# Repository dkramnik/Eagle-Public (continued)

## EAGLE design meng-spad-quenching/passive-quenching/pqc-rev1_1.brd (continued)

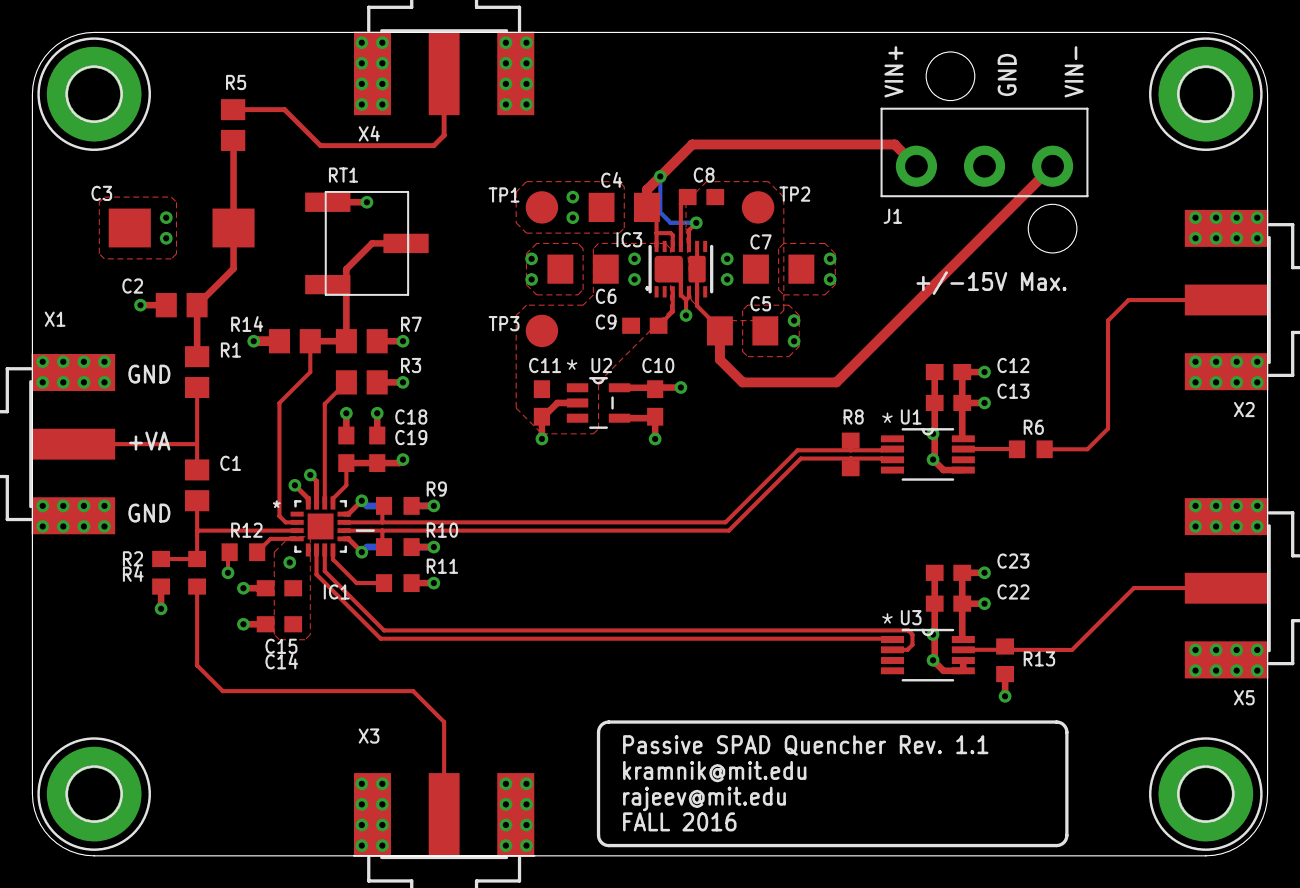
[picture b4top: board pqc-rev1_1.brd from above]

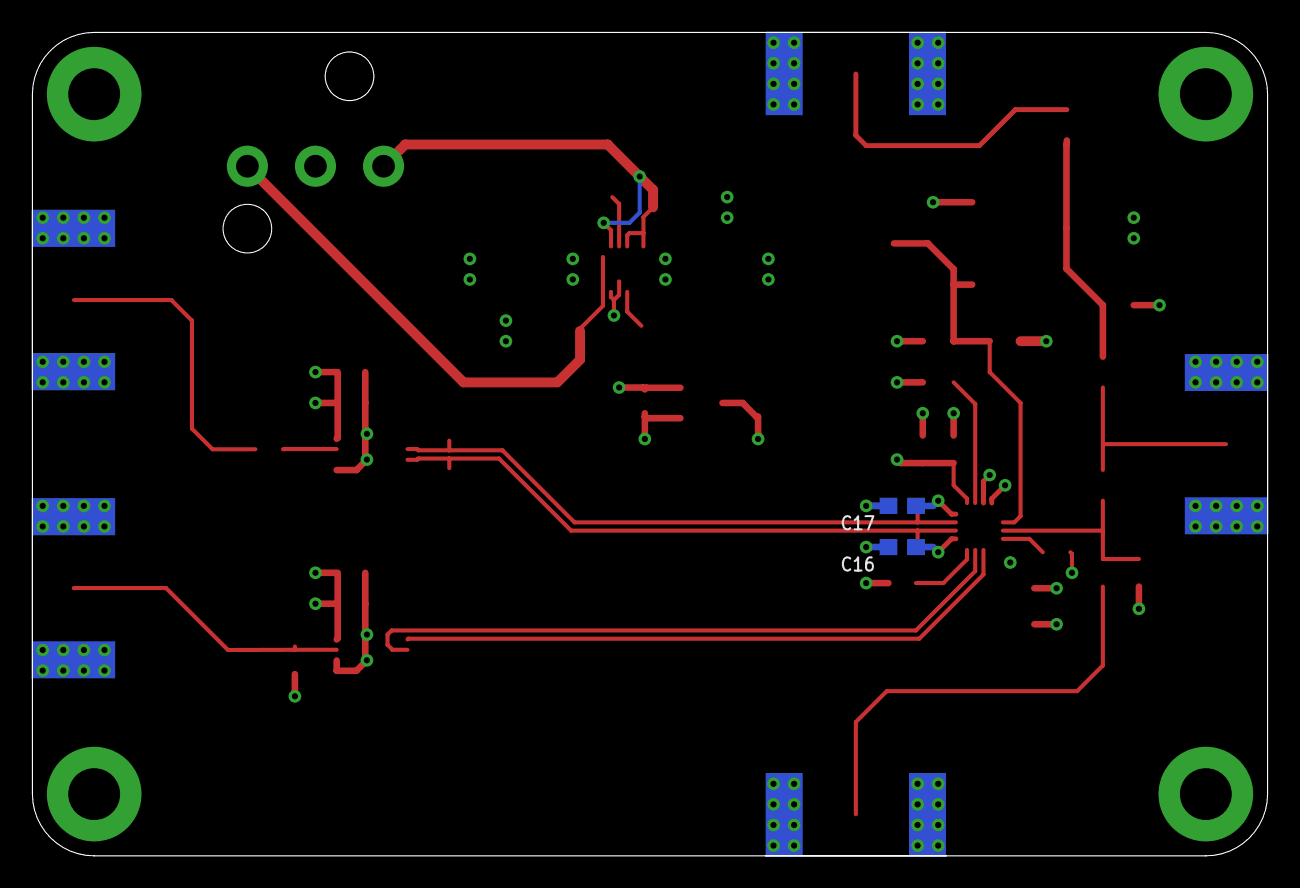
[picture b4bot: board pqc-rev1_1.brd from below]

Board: 4 copper layers, 76.2 x 50.8 mm, 54 parts (2 on the bottom side), 24 nets.

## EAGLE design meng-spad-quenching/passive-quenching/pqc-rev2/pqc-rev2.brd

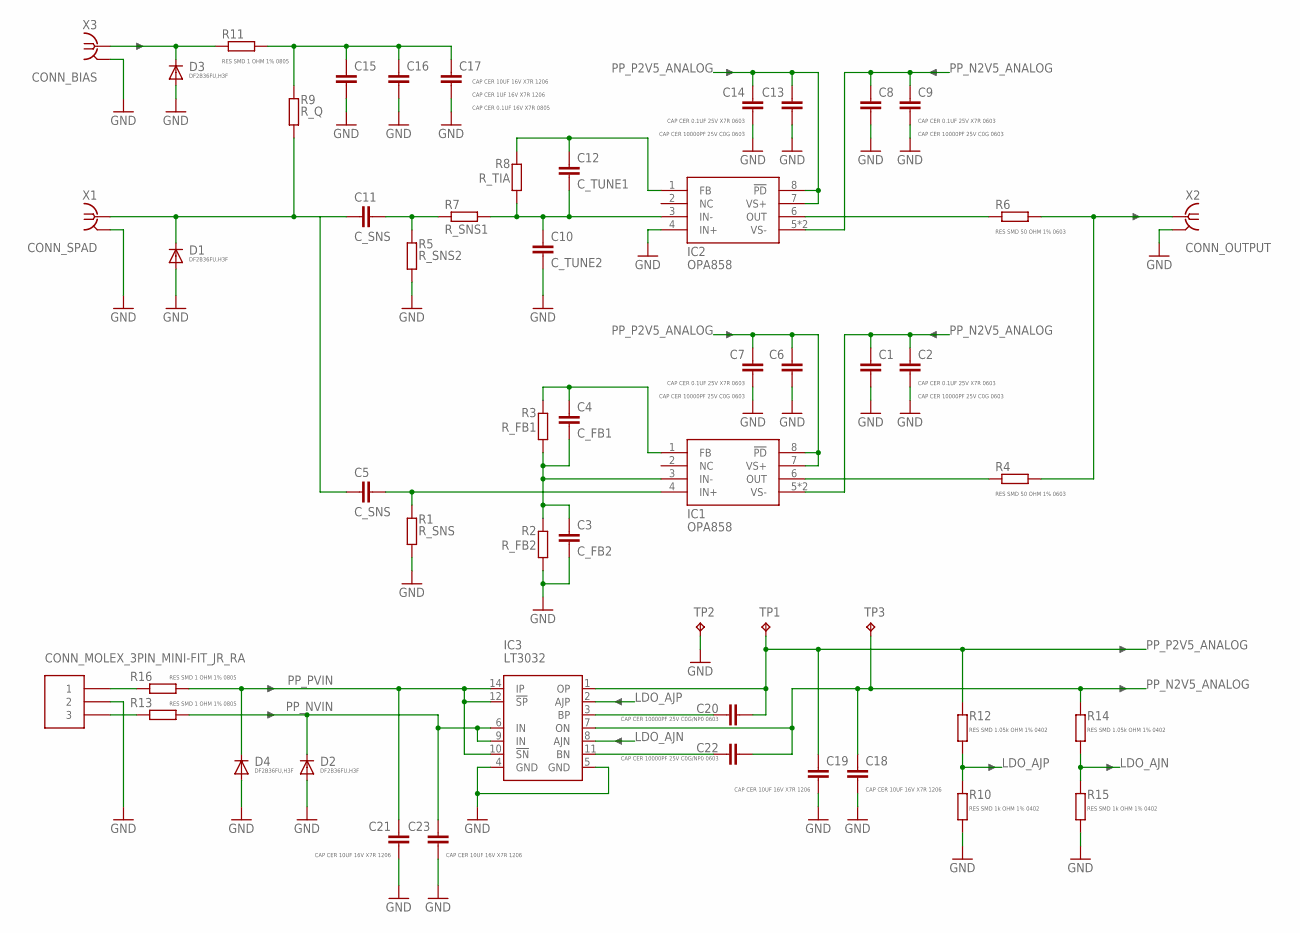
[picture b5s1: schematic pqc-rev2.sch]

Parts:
C1, C6, C8, C13: CAP CER 10000PF 25V C0G 0603; C0603
C2, C7, C9, C14: CAP CER 0.1UF 25V X7R 0603; C0603
C3: C_FB2; C0402
C4: C_FB1; C0402
C5, C11: C_SNS; C0603
C10: C_TUNE2; C0402
C12: C_TUNE1; C0402
C15: CAP CER 0.1UF 16V X7R 0805; C0805
C16: CAP CER 1UF 16V X7R 1206; C1206
C17, C18, C19, C21, C23: CAP CER 10UF 16V X7R 1206; C1206
C20, C22: CAP CER 10000PF 25V C0G/NP0 0603; C0603
D1, D2, D3, D4: DF2B36FU,H3F; SOD323-W
IC1, IC2: OPA858; WSON8
IC3: LT3032; DFN14-4X3DE
J1: CONN_MOLEX_3PIN_MINI-FIT_JR_RA
R1: R_SNS; R0402
R2: R_FB2; R0402
R3: R_FB1; R0402
R4, R6: RES SMD 50 OHM 1% 0603; R0603
R5: R_SNS2; R0402
R7: R_SNS1; R0402
R8: R_TIA; R0402
R9: R_Q; R0805
R10, R15: RES SMD 1k OHM 1% 0402; R0402
R11, R13, R16: RES SMD 1 OHM 1% 0805; R0805
R12, R14: RES SMD 1.05k OHM 1% 0402; R0402
TP1: P2V5; TP20R
TP2: GND; TP20R
TP3: N2V5; TP20R
X1: CONN_SPAD; J502-ND-142-0701-881/886
X2: CONN_OUTPUT; J502-ND-142-0701-881/886
X3: CONN_BIAS; J502-ND-142-0701-881/886

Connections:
GND: C1.2, C2.2, C3.2, C6.2, C7.2, C8.2, C9.2, C10.2, C13.2, C14.2, C15.2, C16.2, C17.2, C18.2, C19.2, C21.2, C23.2, D1.A, D2.A, D3.A, D4.A, IC2.4 (IN+), IC3.4 (GND), IC3.5 (GND), J1.2, R1.1, R2.2, R5.1, R10.2, R15.2, TP2.TP, X1.G@1 (GND), X1.G@2 (GND), X1.G@3 (GND), X1.G@4 (GND), X2.G@1 (GND), X2.G@2 (GND), X2.G@3 (GND), X2.G@4 (GND), X3.G@1 (GND), X3.G@2 (GND), X3.G@3 (GND), X3.G@4 (GND)
LDO_AJN: IC3.8 (AJN), R14.2, R15.1
LDO_AJP: IC3.2 (AJP), R10.1, R12.2
unnamed: C15.1, C16.1, C17.1, R9.2, R11.1
unnamed: C5.1, C11.1, D1.C, R9.1, X1.1
unnamed: C11.2, R5.2, R7.2
unnamed: C10.1, C12.2, IC2.3 (IN-), R7.1, R8.2
unnamed: C12.1, IC2.1 (FB), R8.1
unnamed: C5.2, IC1.4 (IN+), R1.2
unnamed: IC2.6 (OUT), R6.2
unnamed: C20.1, IC3.3 (BP)
unnamed: C22.1, IC3.11 (BN)
unnamed: C3.1, C4.2, IC1.3 (IN-), R2.1, R3.2
unnamed: C4.1, IC1.1 (FB), R3.1
unnamed: R4.1, R6.1, X2.1
unnamed: D3.C, R11.2, X3.1
unnamed: IC1.6 (OUT), R4.2
PP_N2V5_ANALOG: C1.1, C2.1, C8.1, C9.1, C18.1, C22.2, IC1.5 (VS-), IC1.PAD (VS-), IC2.5 (VS-), IC2.PAD (VS-), IC3.7 (ON), R14.1, TP3.TP
PP_NVIN: C23.1, D2.C, IC3.6 (IN), IC3.9 (IN), R13.1
PP_NVIN_CONN: J1.3, R13.2
PP_P2V5_ANALOG: C6.1, C7.1, C13.1, C14.1, C19.1, C20.2, IC1.7 (VS+), IC1.8 (!PD), IC2.7 (VS+), IC2.8 (!PD), IC3.1 (OP), R12.1, TP1.TP
PP_PVIN: C21.1, D4.C, IC3.10 (!SN), IC3.12 (!SP), IC3.14 (IP), R16.1
PP_PVIN_CONN: J1.1, R16.2

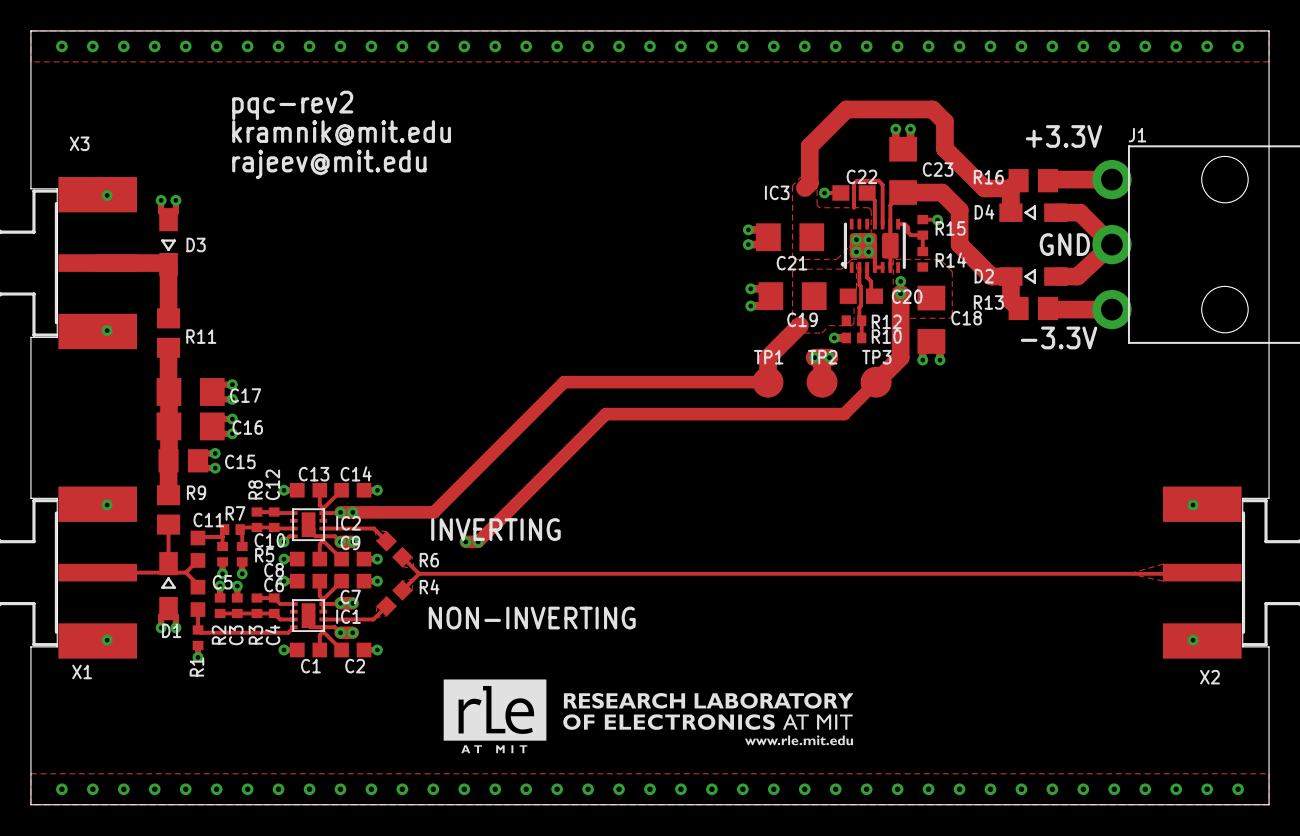
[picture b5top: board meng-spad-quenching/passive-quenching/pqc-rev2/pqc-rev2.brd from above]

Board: 4 copper layers, 80.0 x 50.0 mm, 53 parts (0 on the bottom side), 23 nets.

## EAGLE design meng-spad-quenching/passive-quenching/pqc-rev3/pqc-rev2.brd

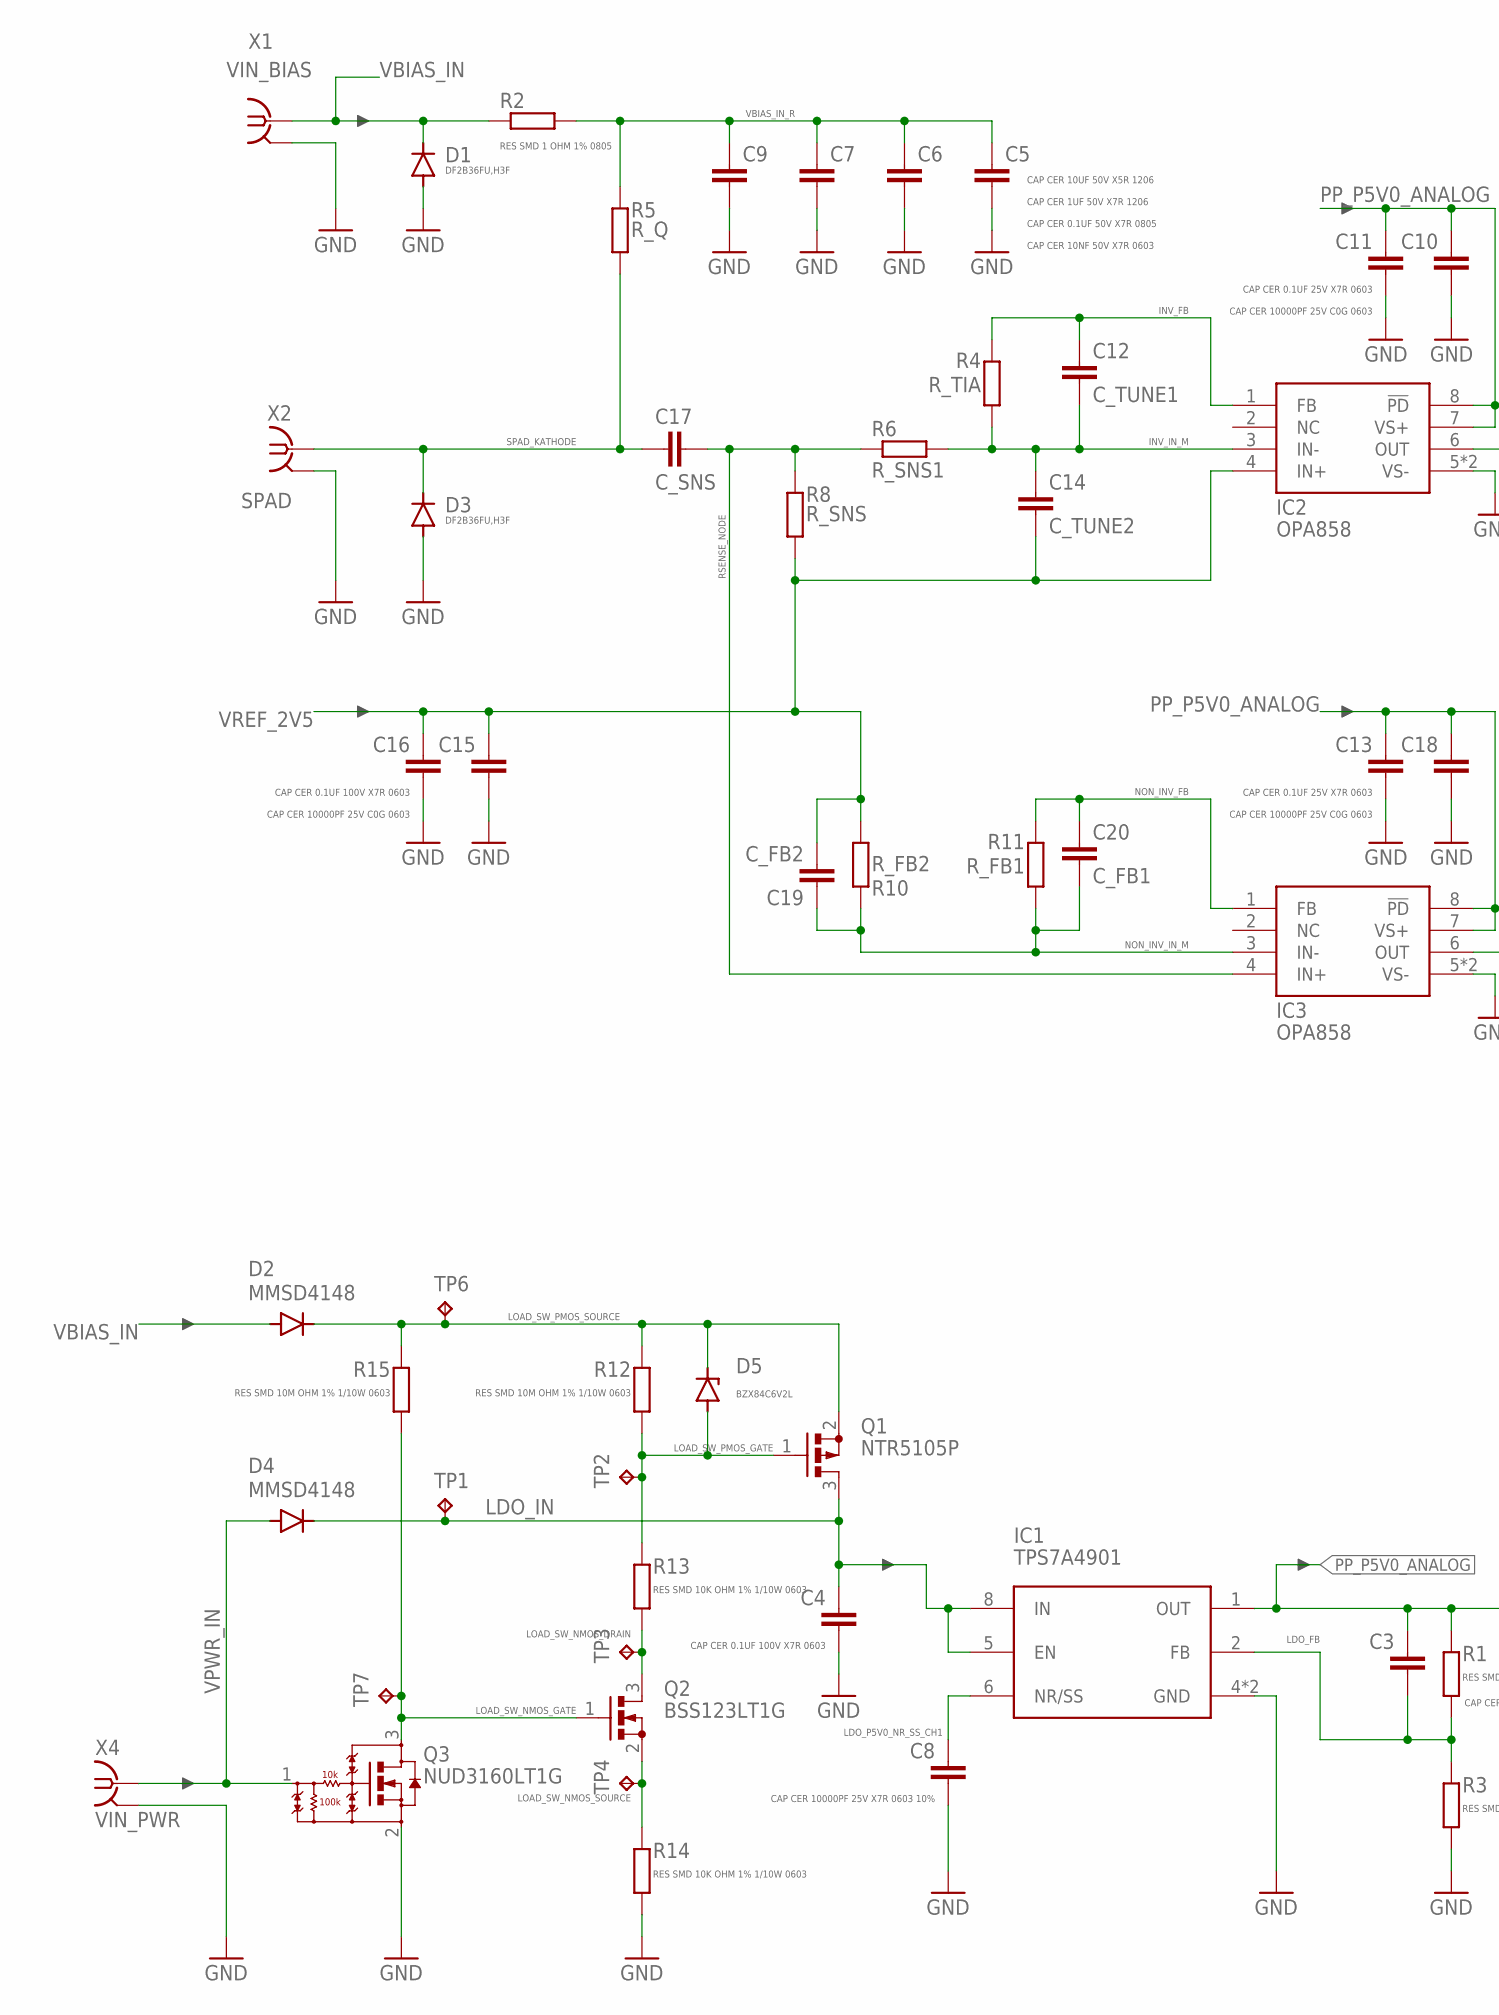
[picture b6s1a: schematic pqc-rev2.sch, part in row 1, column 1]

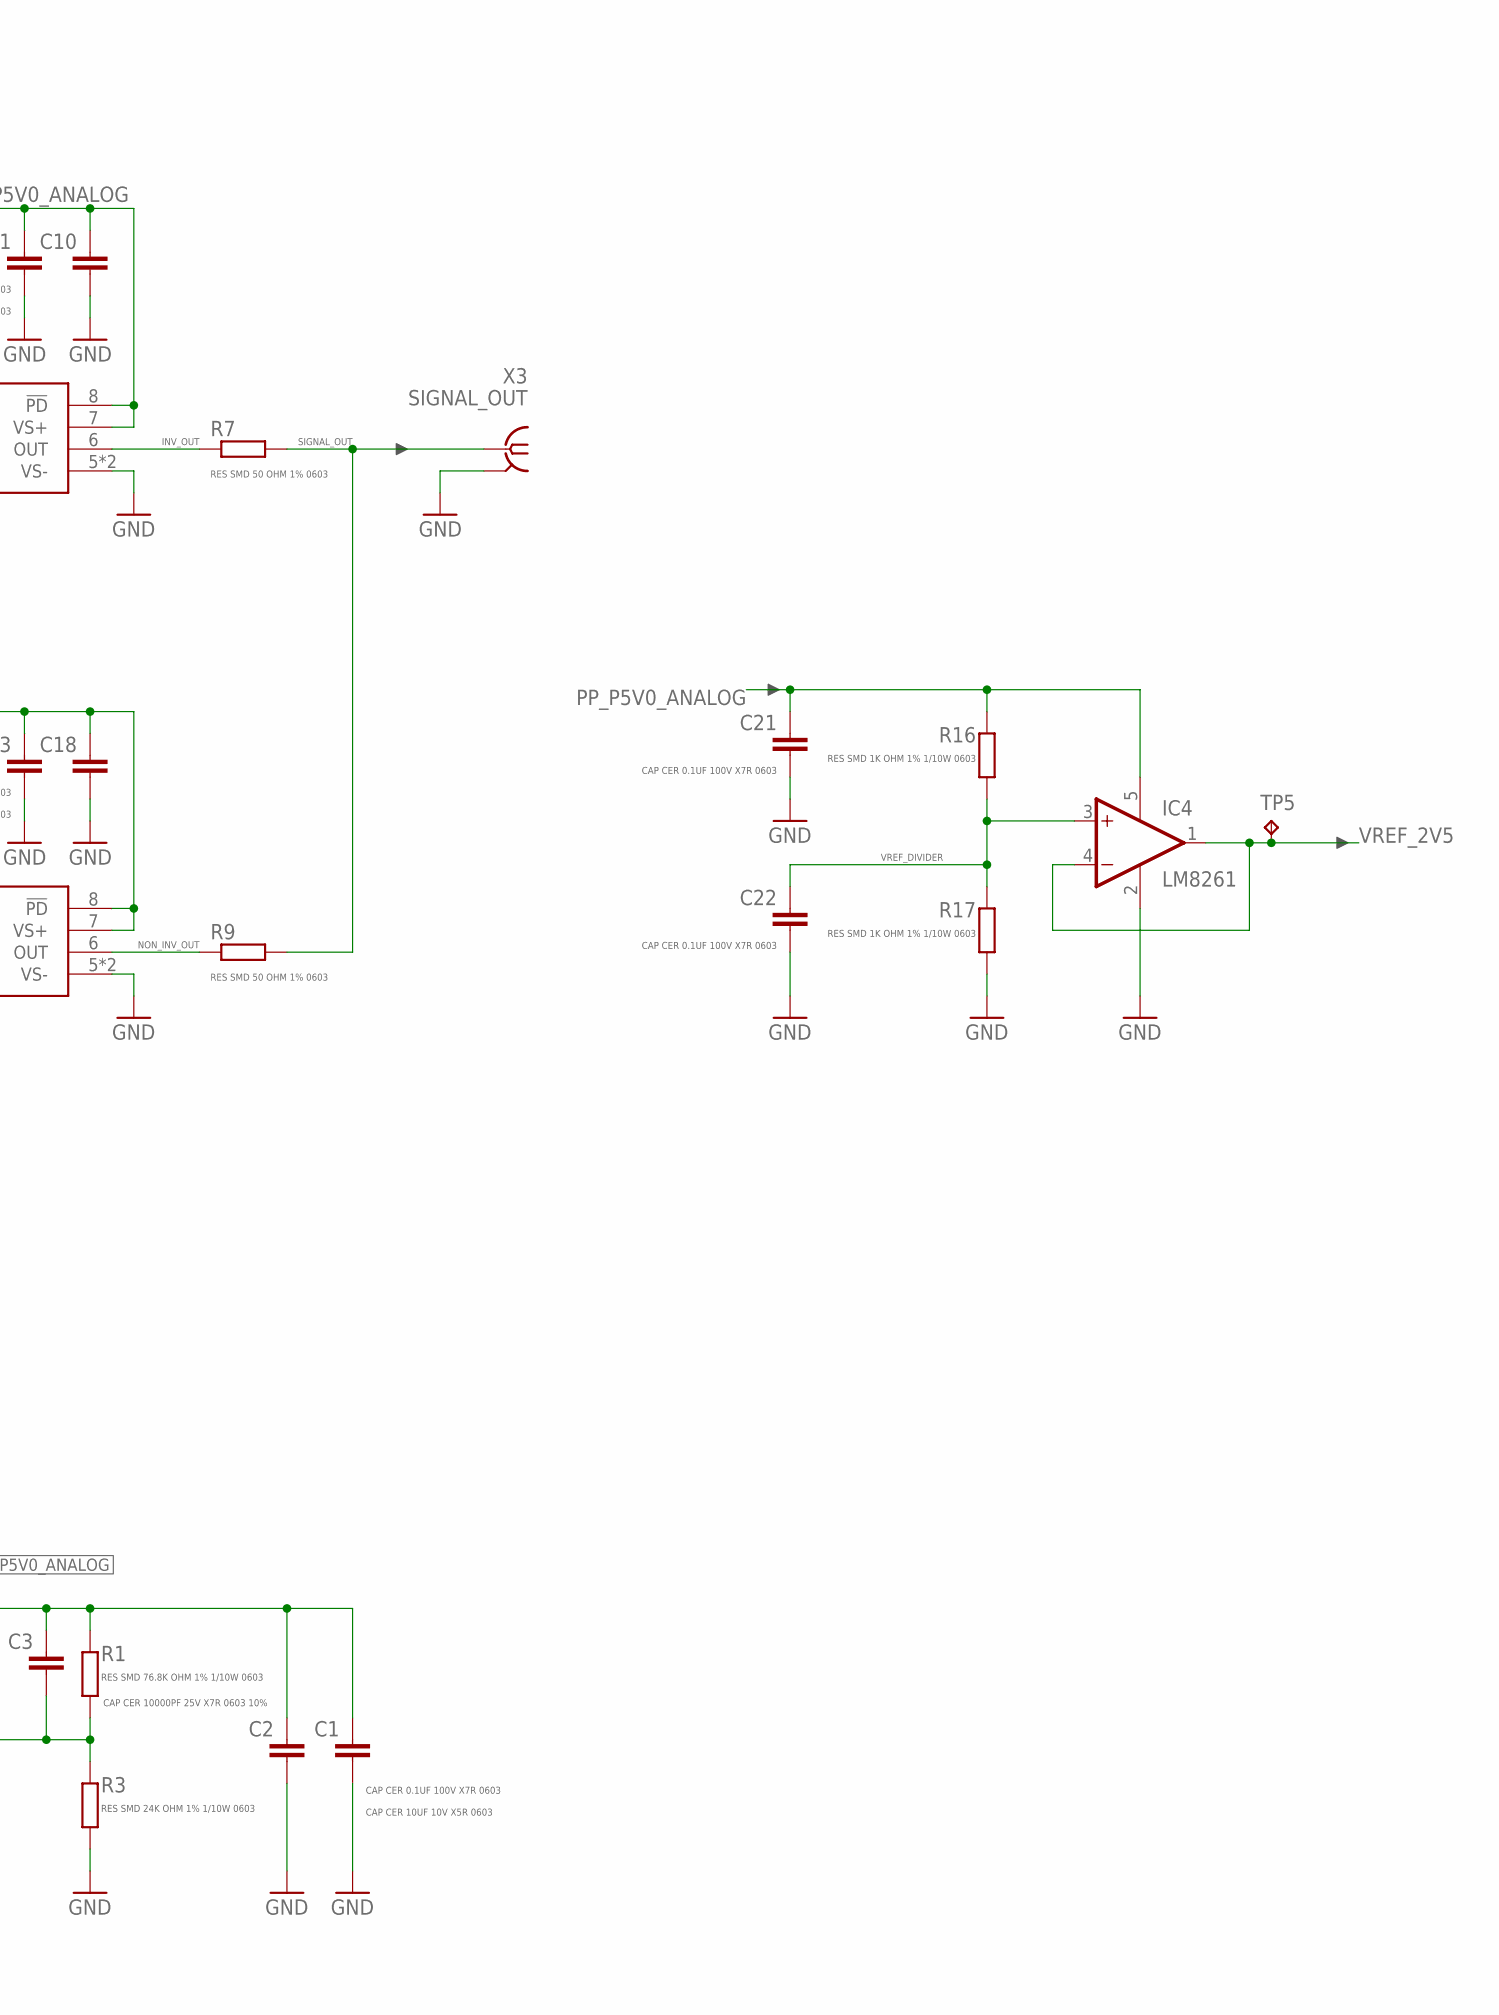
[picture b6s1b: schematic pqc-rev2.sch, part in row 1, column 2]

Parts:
C1: CAP CER 10UF 10V X5R 0603; C0603
C2, C4, C16, C21, C22: CAP CER 0.1UF 100V X7R 0603; C0603
C3, C8: CAP CER 10000PF 25V X7R 0603 10%; C0603
C5: CAP CER 10UF 50V X5R 1206; C1206
C6: CAP CER 1UF 50V X7R 1206; C1206
C7: CAP CER 0.1UF 50V X7R 0805; C0805
C9: CAP CER 10NF 50V X7R 0603; C0603
C10, C15, C18: CAP CER 10000PF 25V C0G 0603; C0603
C11, C13: CAP CER 0.1UF 25V X7R 0603; C0603
C12: C_TUNE1; C0402
C14: C_TUNE2; C0402
C17: C_SNS; C0603
C19: C_FB2; C0402
C20: C_FB1; C0402
D1, D3: DF2B36FU,H3F; SOD323-W
D2, D4: MMSD4148; SOD123
D5: BZX84C6V2L; SOT23
IC1: TPS7A4901; MSOP-8_POWER_PAD
IC2, IC3: OPA858; WSON8
IC4: LM8261; SOT23-5
Q1: NTR5105P; SOT23C
Q2: BSS123LT1G; SOT23C
Q3: NUD3160LT1G; SOT23C
R1: RES SMD 76.8K OHM 1% 1/10W 0603; R0603
R2: RES SMD 1 OHM 1% 0805; R0805
R3: RES SMD 24K OHM 1% 1/10W 0603; R0603
R4: R_TIA; R0402
R5: R_Q; R0805
R6: R_SNS1; R0402
R7, R9: RES SMD 50 OHM 1% 0603; R0603
R8: R_SNS; R0402
R10: R_FB2; R0402
R11: R_FB1; R0402
R12, R15: RES SMD 10M OHM 1% 1/10W 0603; R0603
R13, R14: RES SMD 10K OHM 1% 1/10W 0603; R0603
R16, R17: RES SMD 1K OHM 1% 1/10W 0603; R0603
TP1, TP2, TP3, TP4, TP5, TP6: TPTP10R; TP10R
TP7: TPB1,27; B1,27
X1: VIN_BIAS; MMCX-J-P-X-ST-EM1-MKT
X2: SPAD; J502-ND-142-0701-881/886
X3: SIGNAL_OUT; MMCX-J-P-X-ST-EM1-MKT
X4: VIN_PWR; MMCX-J-P-X-ST-EM1-MKT

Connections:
GND: C1.2, C2.2, C4.2, C5.2, C6.2, C7.2, C8.2, C9.2, C10.2, C11.2, C13.2, C15.2, C16.2, C18.2, C21.2, C22.2, D1.A, D3.A, IC1.4 (GND), IC1.PAD (GND), IC2.5 (VS-), IC2.PAD (VS-), IC3.5 (VS-), IC3.PAD (VS-), IC4.2 (V-), Q3.2 (S), R3.2, R14.1, R17.1, X1.2@1 (GND), X1.2@2 (GND), X1.2@3 (GND), X1.2@4 (GND), X2.G@1 (GND), X2.G@2 (GND), X2.G@3 (GND), X2.G@4 (GND), X3.2@1 (GND), X3.2@2 (GND), X3.2@3 (GND), X3.2@4 (GND), X4.2@1 (GND), X4.2@2 (GND), X4.2@3 (GND), X4.2@4 (GND)
INV_FB: C12.1, IC2.1 (FB), R4.1
INV_IN_M: C12.2, C14.1, IC2.3 (IN-), R4.2, R6.1
INV_OUT: IC2.6 (OUT), R7.2
LDO_FB: C3.2, IC1.2 (FB), R1.1, R3.1
LDO_IN: C4.1, D4.C, IC1.5 (EN), IC1.8 (IN), Q1.3 (D), TP1.TP
LDO_P5V0_NR_SS_CH1: C8.1, IC1.6 (NR/SS)
LOAD_SW_NMOS_DRAIN: Q2.3 (D), R13.1, TP3.TP
LOAD_SW_NMOS_GATE: Q2.1 (G), Q3.3 (D), R15.1, TP7.TP
LOAD_SW_NMOS_SOURCE: Q2.2 (S), R14.2, TP4.TP
LOAD_SW_PMOS_GATE: D5.1 (A), Q1.1 (G), R12.1, R13.2, TP2.TP
LOAD_SW_PMOS_SOURCE: D2.C, D5.3 (C), Q1.2 (S), R12.2, R15.2, TP6.TP
NON_INV_FB: C20.1, IC3.1 (FB), R11.1
NON_INV_IN_M: C19.1, C20.2, IC3.3 (IN-), R10.1, R11.2
NON_INV_OUT: IC3.6 (OUT), R9.2
PP_P5V0_ANALOG: C1.1, C2.1, C3.1, C10.1, C11.1, C13.1, C18.1, C21.1, IC1.1 (OUT), IC2.7 (VS+), IC2.8 (!PD), IC3.7 (VS+), IC3.8 (!PD), IC4.5 (V+), R1.2, R16.2
RSENSE_NODE: C17.2, IC3.4 (IN+), R6.2, R8.2
SIGNAL_OUT: R7.1, R9.1, X3.1
SPAD_KATHODE: C17.1, D3.C, R5.1, X2.1
VBIAS_IN: D1.C, D2.A, R2.2, X1.1
VBIAS_IN_R: C5.1, C6.1, C7.1, C9.1, R2.1, R5.2
VPWR_IN: D4.A, Q3.1 (G), X4.1
VREF_2V5: C14.2, C15.1, C16.1, C19.2, IC2.4 (IN+), IC4.1 (OUT), IC4.4 (-IN), R8.1, R10.2, TP5.TP
VREF_DIVIDER: C22.1, IC4.3 (+IN), R16.1, R17.2

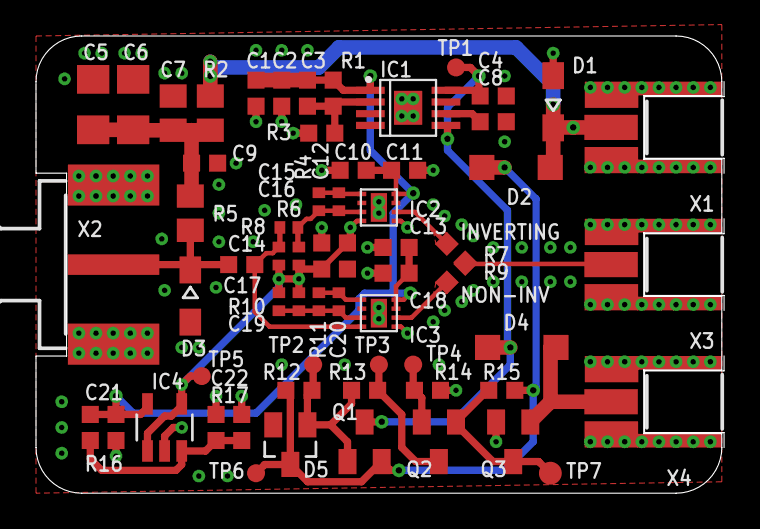
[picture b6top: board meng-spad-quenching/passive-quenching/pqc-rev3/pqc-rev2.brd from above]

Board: 4 copper layers, 38.1 x 25.4 mm, 62 parts (0 on the bottom side), 24 nets.

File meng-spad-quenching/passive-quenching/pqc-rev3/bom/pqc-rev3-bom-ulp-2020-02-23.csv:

"Qty";"Value";"Device";"Package";"Parts";"Description";"MF";"MPN";"OC_FARNELL";"OC_NEWARK";"SPICEPREFIX";"TP_SIGNAL_NAME";"VALUE";
"1";"0R JUMPER 0603";"R-EU_R0603";"R0603";"R1";"RESISTOR, European symbol";"";"";"";"";"";"";"";
"1";"BSS123LT1G";"NMOS_GENERIC";"SOT23C";"Q2";"";"";"";"";"";"";"";"";
"1";"BZX84C6V2L";"ZENER-DIODESOT23";"SOT23";"D5";"Z-Diode";"";"";"";"";"";"";"";
"1";"CAP CER 0.1PF 50V C0G/NP0 0402";"C-EUC0402";"C0402";"C20";"CAPACITOR, European symbol";"";"";"";"";"";"";"";
"5";"CAP CER 0.1UF 100V X7R 0603";"C-EUC0603";"C0603";"C2, C4, C16, C21, C22";"CAPACITOR, European symbol";"";"";"";"";"";"";"";
"2";"CAP CER 0.1UF 25V X7R 0603";"C-EUC0603";"C0603";"C11, C13";"CAPACITOR, European symbol";"";"";"";"";"";"";"";
"1";"CAP CER 0.1UF 50V X7R 0805";"C-EUC0805";"C0805";"C7";"CAPACITOR, European symbol";"";"";"";"";"";"";"";
"3";"CAP CER 10000PF 25V C0G 0603";"C-EUC0603";"C0603";"C10, C15, C18";"CAPACITOR, European symbol";"";"";"";"";"";"";"";
"1";"CAP CER 10000PF 25V X7R 0603 10%";"C-EUC0603";"C0603";"C8";"CAPACITOR, European symbol";"";"";"";"";"";"";"";
"1";"CAP CER 10NF 50V X7R 0603";"C-EUC0603";"C0603";"C9";"CAPACITOR, European symbol";"";"";"";"";"";"";"";
"1";"CAP CER 10PF 250V C0G/NP0 0603";"C-EUC0603";"C0603";"C17";"CAPACITOR, European symbol";"";"";"";"";"";"";"";
"1";"CAP CER 10UF 10V X5R 0603";"C-EUC0603";"C0603";"C1";"CAPACITOR, European symbol";"";"";"";"";"";"";"";
"1";"CAP CER 10UF 50V X5R 1206";"C-EUC1206";"C1206";"C5";"CAPACITOR, European symbol";"";"";"";"";"";"";"";
"1";"CAP CER 1UF 50V X7R 1206";"C-EUC1206";"C1206";"C6";"CAPACITOR, European symbol";"";"";"";"";"";"";"";
"1";"D55V0M1B2WS-7";"DIODE-SOD323-W";"SOD323-W";"D1";"DIODE";"";"";"";"";"";"";"";
"3";"DNP";"C-EUC0402";"C0402";"C12, C14, C19";"CAPACITOR, European symbol";"";"";"";"";"";"";"";
"1";"DNP";"C-EUC0603";"C0603";"C3";"CAPACITOR, European symbol";"";"";"";"";"";"";"";
"1";"DNP";"DIODE-SOD323-W";"SOD323-W";"D3";"DIODE";"";"";"";"";"";"";"";
"1";"DNP";"OPA858";"WSON8";"IC2";"";"";"";"";"";"";"";"OPA858";
"2";"DNP";"R-EU_R0402";"R0402";"R4, R6";"RESISTOR, European symbol";"";"";"";"";"";"";"";
"2";"DNP";"R-EU_R0603";"R0603";"R3, R7";"RESISTOR, European symbol";"";"";"";"";"";"";"";
"1";"LM8261";"LM8261";"SOT23-5";"IC4";"";"";"";"";"";"";"";"LM8261";
"2";"MMSD4148";"DIODE-SOD123";"SOD123";"D2, D4";"DIODE";"";"";"";"";"";"";"";
"1";"NTR5105P";"PMOS_GENERIC_SOT23-3";"SOT23C";"Q1";"";"";"";"";"";"";"";"";
"1";"NUD3160LT1G";"NUD3160LT1G";"SOT23C";"Q3";"";"";"";"";"";"";"";"NUD3160LT1G";
"1";"OPA858";"OPA858";"WSON8";"IC3";"";"";"";"";"";"";"";"OPA858";
"1";"RES SMD 1 OHM 1% 0805";"R-EU_R0805";"R0805";"R2";"RESISTOR, European symbol";"";"";"";"";"R";"";"";
"1";"RES SMD 100 OHM 1% 0402";"R-EU_R0402";"R0402";"R10";"RESISTOR, European symbol";"";"";"";"";"";"";"";
"1";"RES SMD 100K OHM 1% 0805";"R-EU_R0805";"R0805";"R5";"RESISTOR, European symbol";"";"";"";"";"R";"";"";
"2";"RES SMD 10K OHM 1% 1/10W 0603";"R-EU_R0603";"R0603";"R13, R14";"RESISTOR, European symbol";"";"";"";"";"";"";"";
"2";"RES SMD 10M OHM 1% 1/10W 0603";"R-EU_R0603";"R0603";"R12, R15";"RESISTOR, European symbol";"";"";"";"";"";"";"";
"1";"RES SMD 1K OHM 1% 0402";"R-EU_R0402";"R0402";"R11";"RESISTOR, European symbol";"";"";"";"";"";"";"";
"2";"RES SMD 1K OHM 1% 1/10W 0603";"R-EU_R0603";"R0603";"R16, R17";"RESISTOR, European symbol";"";"";"";"";"";"";"";
"1";"RES SMD 50 OHM 1% 0402";"R-EU_R0402";"R0402";"R8";"RESISTOR, European symbol";"";"";"";"";"";"";"";
"1";"RES SMD 50 OHM 1% 0603";"R-EU_R0603";"R0603";"R9";"RESISTOR, European symbol";"";"";"";"";"";"";"";
"1";"SIGNAL_OUT";"COAX";"MMCX-J-P-X-ST-EM1-MKT";"X3";"MMCX STRAIGHT, EDGE MOUNT JACK- 50 OHM";"Samtec Inc.";"MMCX-J-P-X-ST-EM1-MKT";"unknown";"unknown";"";"";"";
"1";"SPAD";"SMA-142-0701-881/886";"J502-ND-142-0701-881/886";"X2";"SMA 50 Ohm End Launch Jack Receptacle - Round Contact";"JOHNSON COMPONENTS";"142-0701-881";"1608603";"08B906";"";"";"";
"1";"TPB1,27";"TPB1,27";"B1,27";"TP7";"Test pad";"";"";"";"";"";"";"";
"1";"TPS79850";"TPS7A";"MSOP-8_POWER_PAD";"IC1";"";"";"";"";"";"";"";"";
"6";"TPTP10R";"TPTP10R";"TP10R";"TP1, TP2, TP3, TP4, TP5, TP6";"Test pad";"";"";"";"";"";"";"";
"1";"VIN_BIAS";"COAX";"MMCX-J-P-X-ST-EM1-MKT";"X1";"MMCX STRAIGHT, EDGE MOUNT JACK- 50 OHM";"Samtec Inc.";"MMCX-J-P-X-ST-EM1-MKT";"unknown";"unknown";"";"";"";
"1";"VIN_PWR";"COAX";"MMCX-J-P-X-ST-EM1-MKT";"X4";"MMCX STRAIGHT, EDGE MOUNT JACK- 50 OHM";"Samtec Inc.";"MMCX-J-P-X-ST-EM1-MKT";"unknown";"unknown";"";"";"";
